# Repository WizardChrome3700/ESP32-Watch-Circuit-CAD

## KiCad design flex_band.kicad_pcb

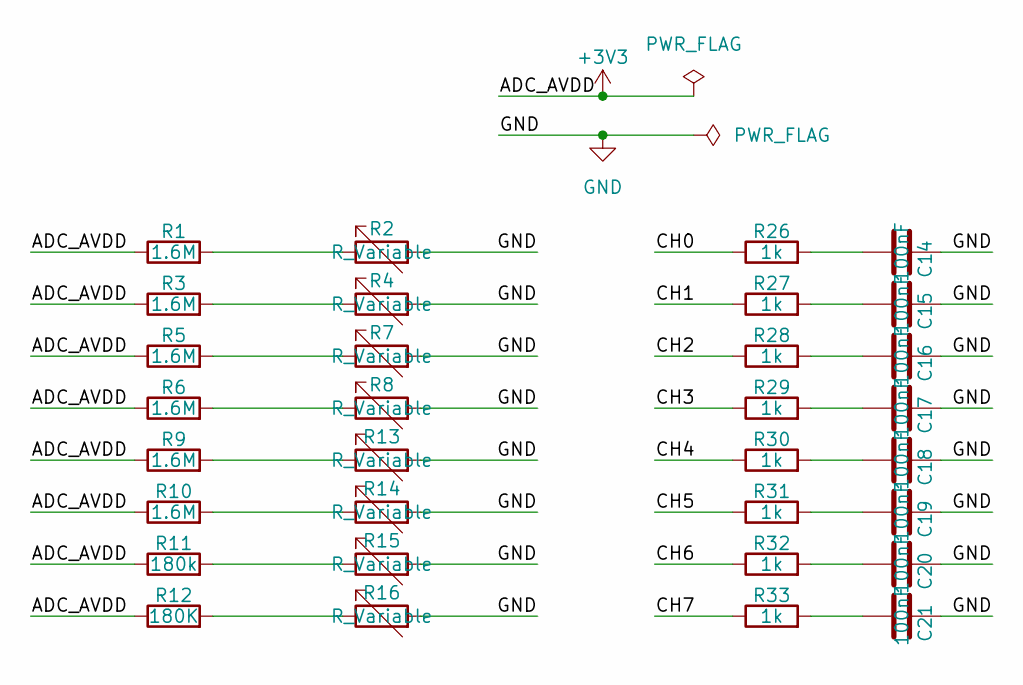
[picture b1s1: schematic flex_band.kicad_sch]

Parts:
C14, C15, C16, C17, C18, C19, C20, C21: 100nF; C_01005_0402Metric_Pad0.57x0.30mm_HandSolder
R1, R3, R5, R6, R9, R10: 1.6M; R_0805_2012Metric_Pad1.20x1.40mm_HandSolder
R2, R4, R7, R8, R13, R14, R15, R16: R_Variable; FSR_15mm
R11: 180k; R_0805_2012Metric_Pad1.20x1.40mm_HandSolder
R12: 180K; R_0805_2012Metric_Pad1.20x1.40mm_HandSolder
R26, R27, R28, R29, R30, R31, R32, R33: 1k; R_1206_3216Metric

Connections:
+3V3: R1.1, R3.1, R5.1, R6.1, R9.1, R10.1, R11.1, R12.1
/CH0: R26.1
/CH1: R27.1
/CH2: R28.1
/CH3: R29.1
/CH4: R30.1
/CH5: R31.1
/CH6: R32.1
/CH7: R33.1
GND: C14.1, C15.1, C16.1, C17.1, C18.1, C19.1, C20.1, C21.1, R2.2, R4.2, R7.2, R8.2, R13.2, R14.2, R15.2, R16.2
unnamed: C14.2, R26.2
unnamed: C15.2, R27.2
unnamed: C16.2, R28.2
unnamed: C17.2, R29.2
unnamed: C18.2, R30.2
unnamed: C19.2, R31.2
unnamed: C20.2, R32.2
unnamed: C21.2, R33.2
unnamed: R1.2, R2.1
unnamed: R3.2, R4.1
unnamed: R5.2, R7.1
unnamed: R6.2, R8.1
unnamed: R10.2, R14.1
unnamed: R11.2, R15.1
unnamed: R12.2, R16.1
unnamed: R9.2, R13.1

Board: 2 copper layers, 32 parts (0 on the bottom side), 18 nets, no tracks yet.

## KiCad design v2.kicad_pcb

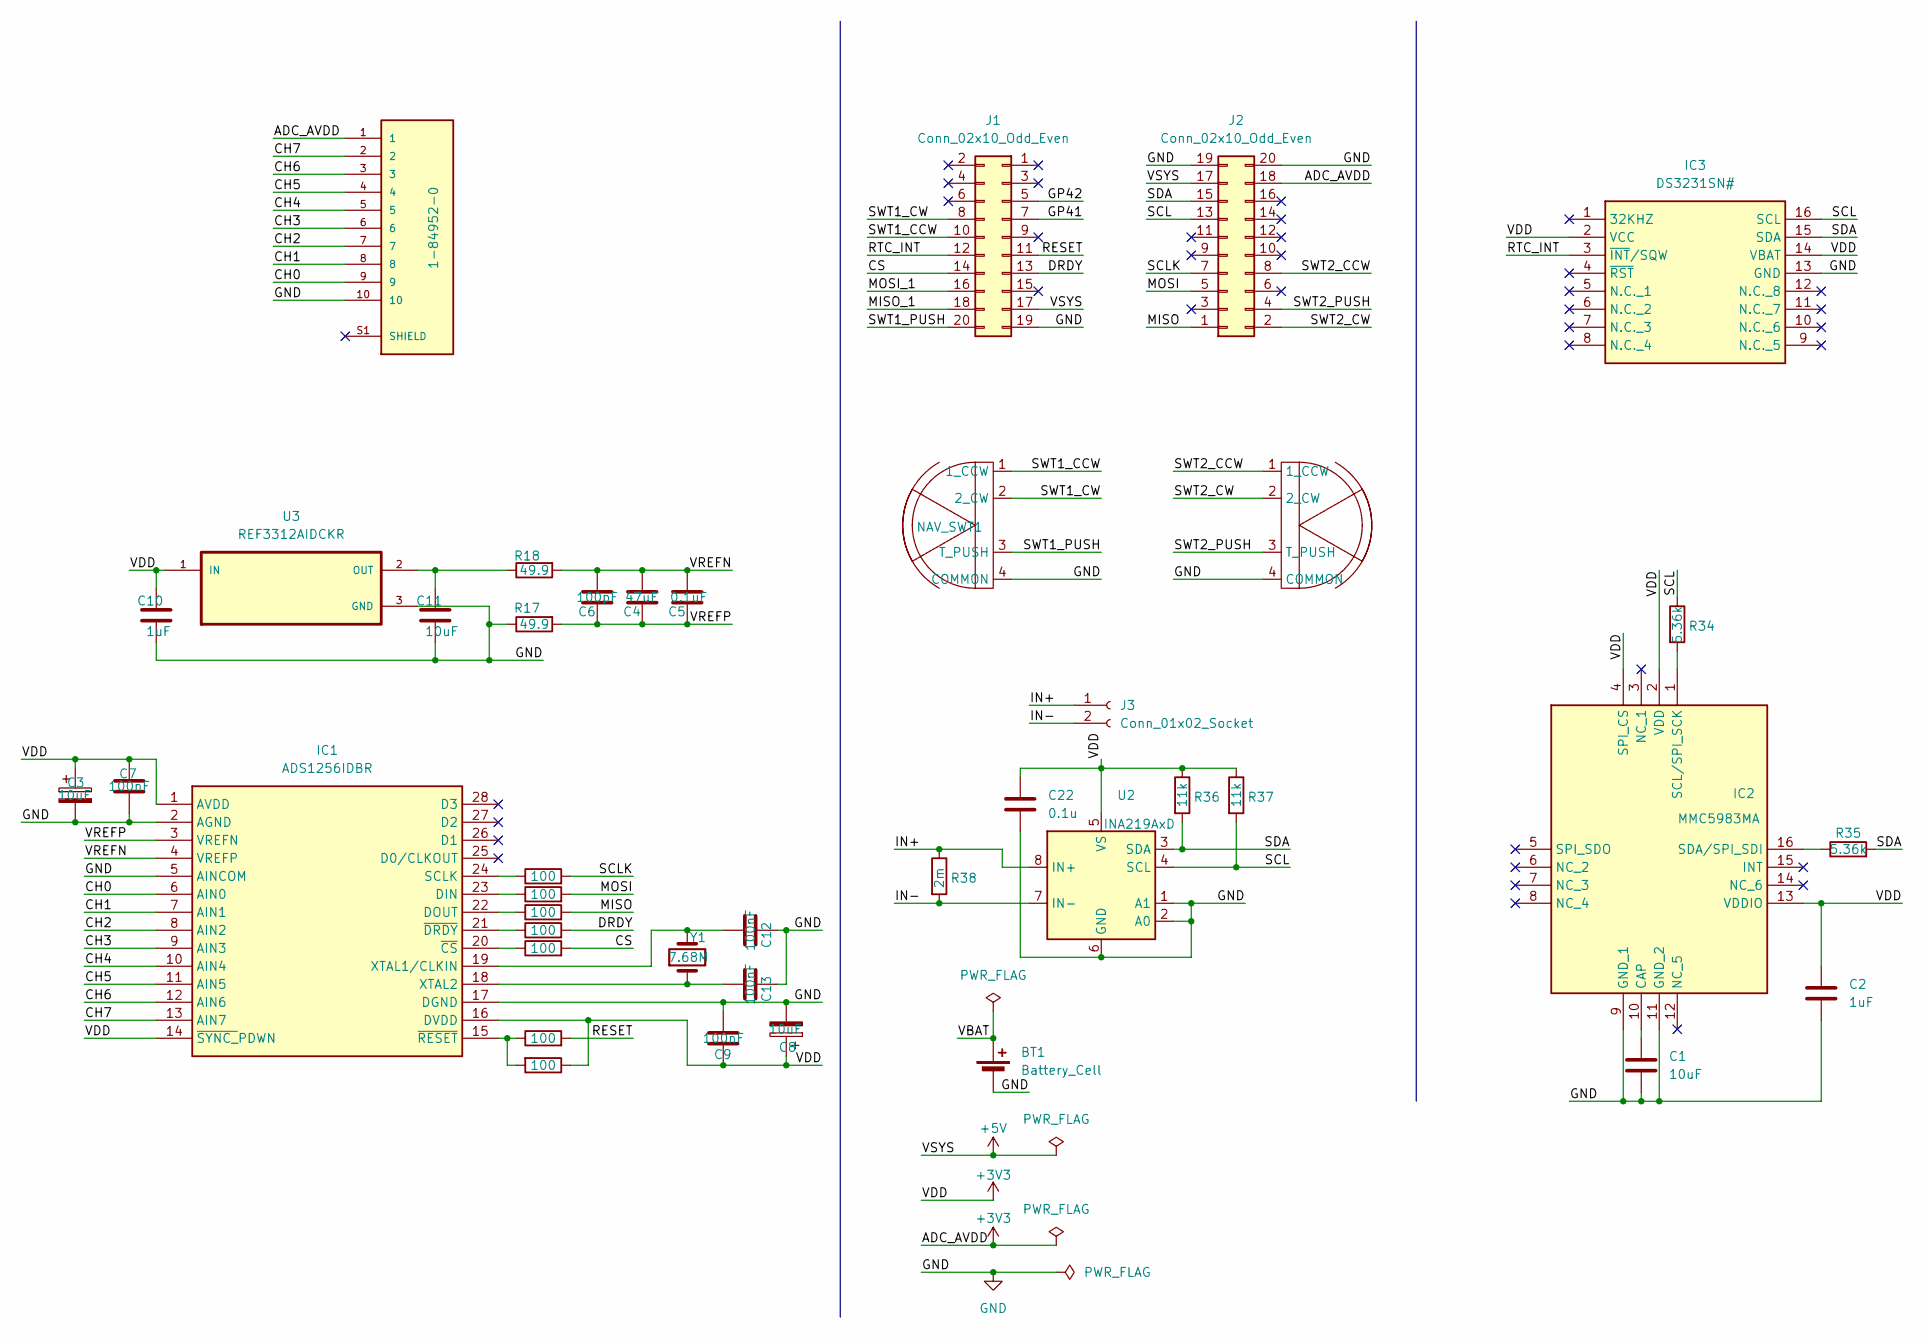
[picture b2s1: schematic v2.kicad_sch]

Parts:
BT1: Battery_Cell; BatteryHolder_Keystone_1060_1x2032
C1: 10uF; C_0603_1608Metric_Pad1.08x0.95mm_HandSolder
C2: 1uF; C_0603_1608Metric_Pad1.08x0.95mm_HandSolder
C3, C8: 10uF; CP_EIA-6032-28_Kemet-C_HandSolder
C4: 47uF; C_0201_0603Metric_Pad0.64x0.40mm_HandSolder
C5: 0.1uF; C_01005_0402Metric
C6: 100pF; C_0603_1608Metric
C7, C9, C12, C13: 100nF; C_01005_0402Metric_Pad0.57x0.30mm_HandSolder
C10: 1uF; C_0805_2012Metric
C11: 10uF; C_0805_2012Metric
C22: 0.1u; C_0402_1005Metric_Pad0.74x0.62mm_HandSolder
IC1: ADS1256IDBR; SOP65P780X200-28N; Mouser Part Number 595-ADS1256IDBR
IC2: MMC5983MA; Mouser Part Number 438-MMC5983MA
IC3: DS3231SN#; SOIC127P1032X265-16N; Mouser Part Number 700-DS3231SN#
J1, J2: Conn_02x10_Odd_Even; PinHeader_2x10_P1.27mm_Vertical_SMD
J3: Conn_01x02_Socket; JST_PH_S2B-PH-K_1x02_P2.00mm_Horizontal
J4: 1-84952-0; TE_1-84952-0; PARTREV A4
NAV_SWT1, NAV_SWT2: 3 Way Navigation Switch
R17, R18: 49.9; R_0805_2012Metric
R19, R20, R21, R22, R23, R24, R25: 100; R_0402_1005Metric_Pad0.72x0.64mm_HandSolder
R34, R35: 5.36k; R_1206_3216Metric_Pad1.30x1.75mm_HandSolder
R36, R37: 11k; R_1206_3216Metric_Pad1.30x1.75mm_HandSolder
R38: 2m; R_2816_7142Metric
U2: INA219AxD; SOIC-8_3.9x4.9mm_P1.27mm
U3: REF3312AIDCKR; SOT65P210X110-3N; DIGI-KEY_PART_NUMBER 296-22636-1-ND
Y1: 7.68M; Crystal_HC49-4H_Vertical

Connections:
+3V3: C2.1, C3.1, C7.1, C8.1, C9.1, C10.1, C22.1, IC1.1 (AVDD), IC1.14 (~SYNC_PDWN), IC1.16 (DVDD), IC2.2 (VDD), IC2.4 (SPI_CS), IC2.13 (VDDIO), IC3.2 (VCC), IC3.14 (VBAT), J2.18, J4.1, R25.1, R36.1, R37.1, U2.5 (VS), U3.1 (IN)
+5V: J1.17, J2.17
/CH0: IC1.6 (AIN0), J4.9
/CH1: IC1.7 (AIN1), J4.8
/CH2: IC1.8 (AIN2), J4.7
/CH3: IC1.9 (AIN3), J4.6
/CH4: IC1.10 (AIN4), J4.5
/CH5: IC1.11 (AIN5), J4.4
/CH6: IC1.12 (AIN6), J4.3
/CH7: IC1.13 (AIN7), J4.2
/CS: J1.14, R23.2
/DRDY: J1.13, R22.2
/GP41: J1.7
/GP42: J1.5
/IN+: J3.1, R38.1, U2.8 (IN+)
/IN-: J3.2, R38.2, U2.7 (IN-)
/MISO: J2.1, R21.2
/MISO_1: J1.18
/MOSI: J2.5, R20.2
/MOSI_1: J1.16
/RESET: J1.11, R24.2
/RTC_INT: IC3.3 (~INT/SQW), J1.12
/SCL: IC3.16 (SCL), J2.13, R34.1, R37.2, U2.4 (SCL)
/SCLK: J2.7, R19.2
/SDA: IC3.15 (SDA), J2.15, R35.2, R36.2, U2.3 (SDA)
/SWT1_CCW: J1.10, NAV_SWT1.1 (1_CCW)
/SWT1_CW: J1.8, NAV_SWT1.2 (2_CW)
/SWT1_PUSH: J1.20, NAV_SWT1.3 (T_PUSH)
/SWT2_CCW: J2.8, NAV_SWT2.1 (1_CCW)
/SWT2_CW: J2.2, NAV_SWT2.2 (2_CW)
/SWT2_PUSH: J2.4, NAV_SWT2.3 (T_PUSH)
/VREFN: C4.2, C5.2, C6.2, IC1.4 (VREFP), R18.2
/VREFP: C4.1, C5.1, C6.1, IC1.3 (VREFN), R17.2
GND: BT1.2 (-), C1.2, C2.2, C3.2, C7.2, C8.2, C9.2, C10.2, C11.2, C12.1, C13.1, C22.2, IC1.2 (AGND), IC1.5 (AINCOM), IC1.17 (DGND), IC2.9 (GND_1), IC2.11 (GND_2), IC3.13 (GND), J1.19, J2.19, J2.20, J4.10, NAV_SWT1.4 (COMMON), NAV_SWT2.4 (COMMON), R17.1, U2.1 (A1), U2.2 (A0), U2.6 (GND), U3.3 (GND)
unnamed: IC1.23 (DIN), R20.1
unnamed: IC1.22 (DOUT), R21.1
unnamed: IC1.24 (SCLK), R19.1
unnamed: C12.2, IC1.19 (XTAL1/CLKIN), Y1.2
unnamed: C13.2, IC1.18 (XTAL2), Y1.1
unnamed: IC1.20 (~CS), R23.1
unnamed: IC1.21 (~DRDY), R22.1
unnamed: IC1.15 (~RESET), R24.1, R25.2
unnamed: C1.1, IC2.10 (CAP)
unnamed: IC2.1 (SCL/SPI_SCK), R34.2
unnamed: IC2.16 (SDA/SPI_SDI), R35.1
unnamed: C11.1, R18.1, U3.2 (OUT)

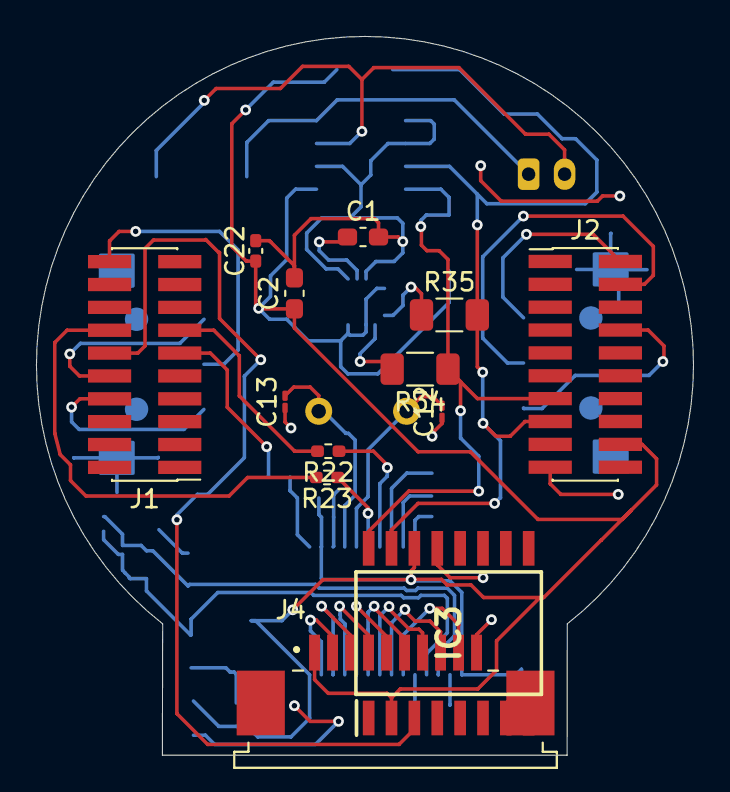
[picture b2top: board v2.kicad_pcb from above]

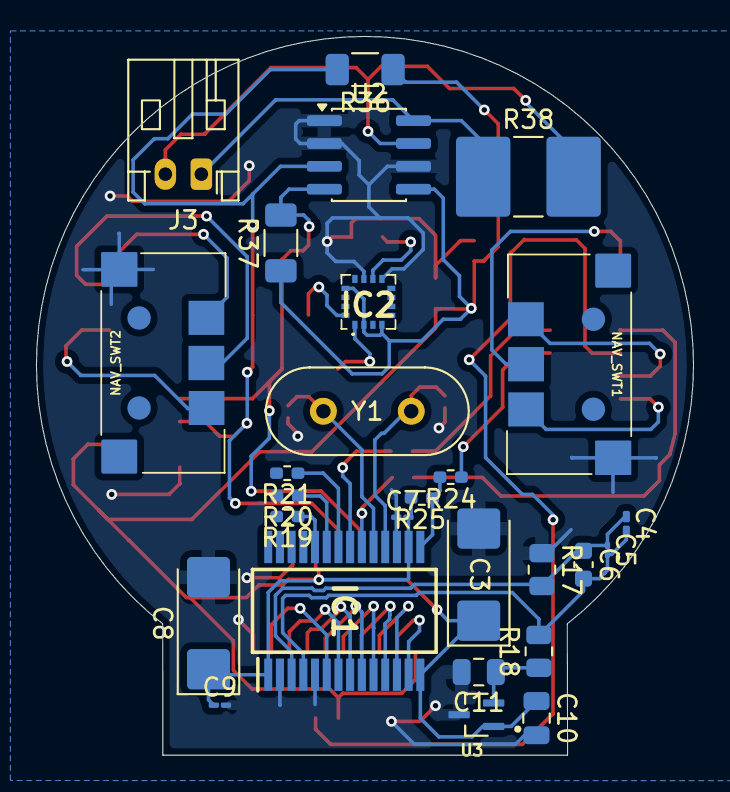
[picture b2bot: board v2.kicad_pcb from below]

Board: 2 copper layers, 36.5 x 39.9 mm, 40 parts (27 on the bottom side), 42 nets.
